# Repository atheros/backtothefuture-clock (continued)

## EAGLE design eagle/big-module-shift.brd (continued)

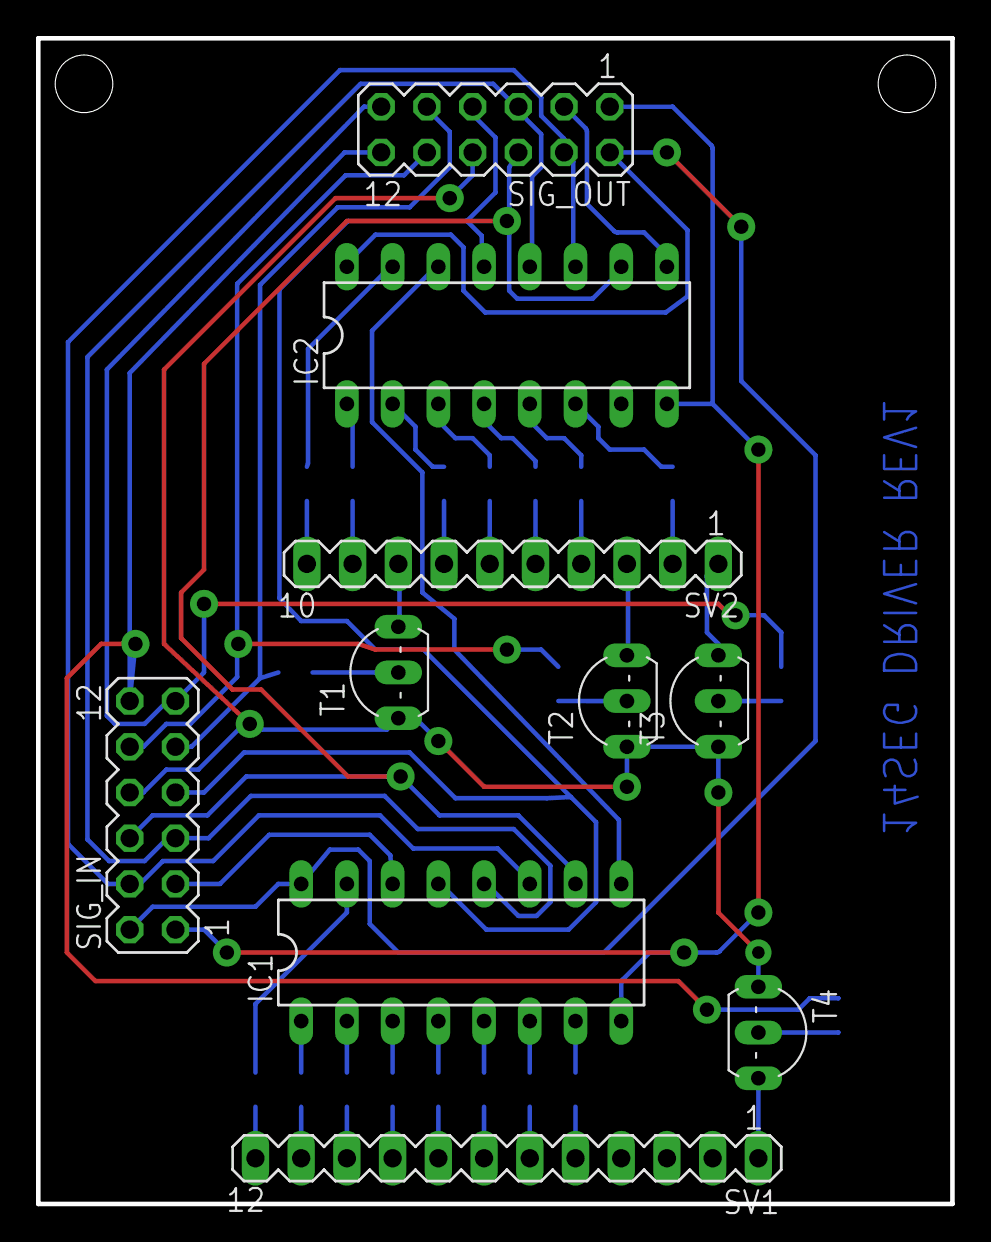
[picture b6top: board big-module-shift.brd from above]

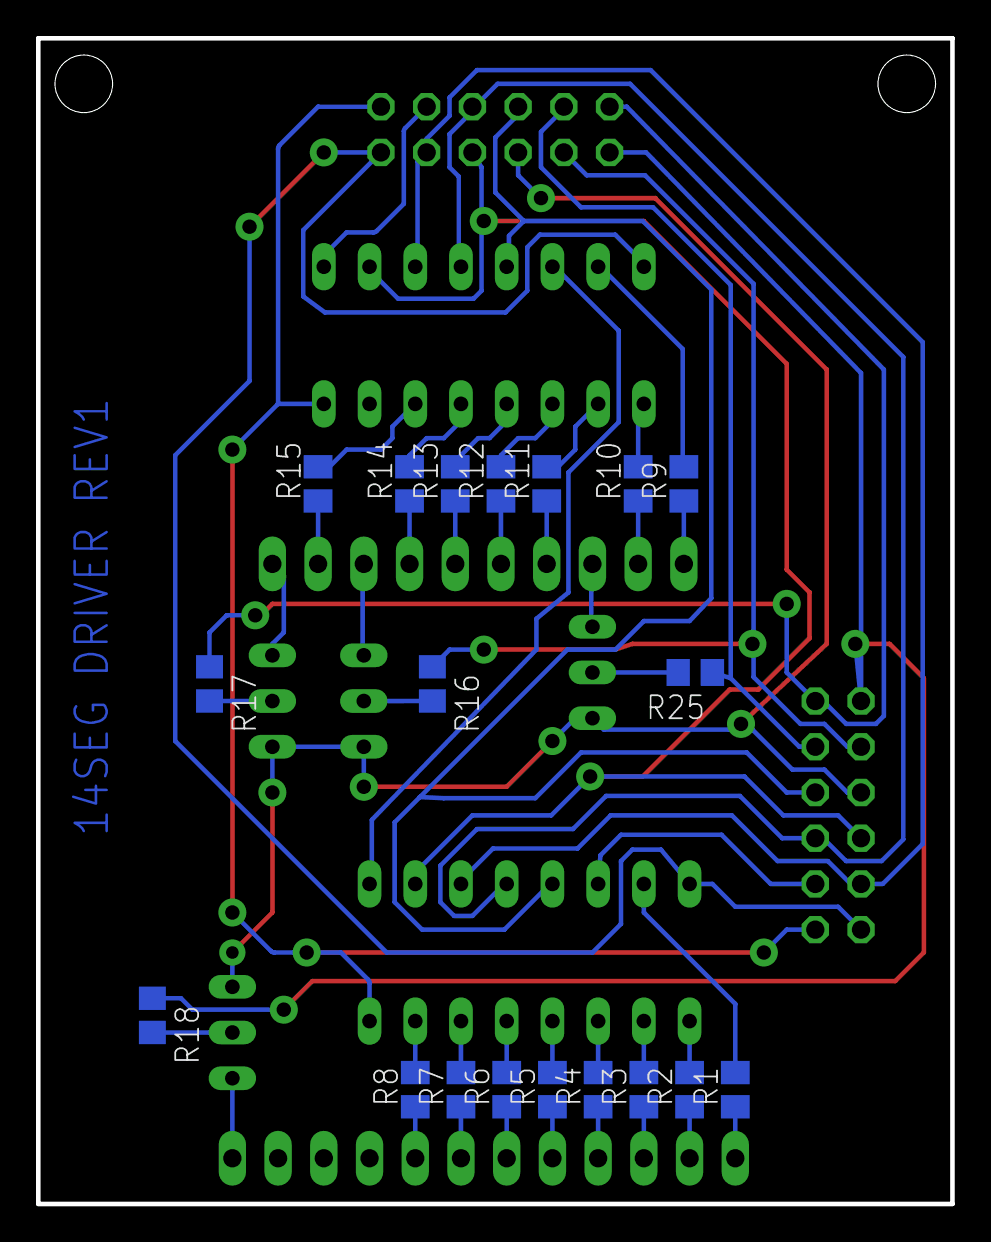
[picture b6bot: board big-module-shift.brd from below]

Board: 2 copper layers, 50.8 x 64.8 mm, 29 parts (19 on the bottom side), 52 nets.

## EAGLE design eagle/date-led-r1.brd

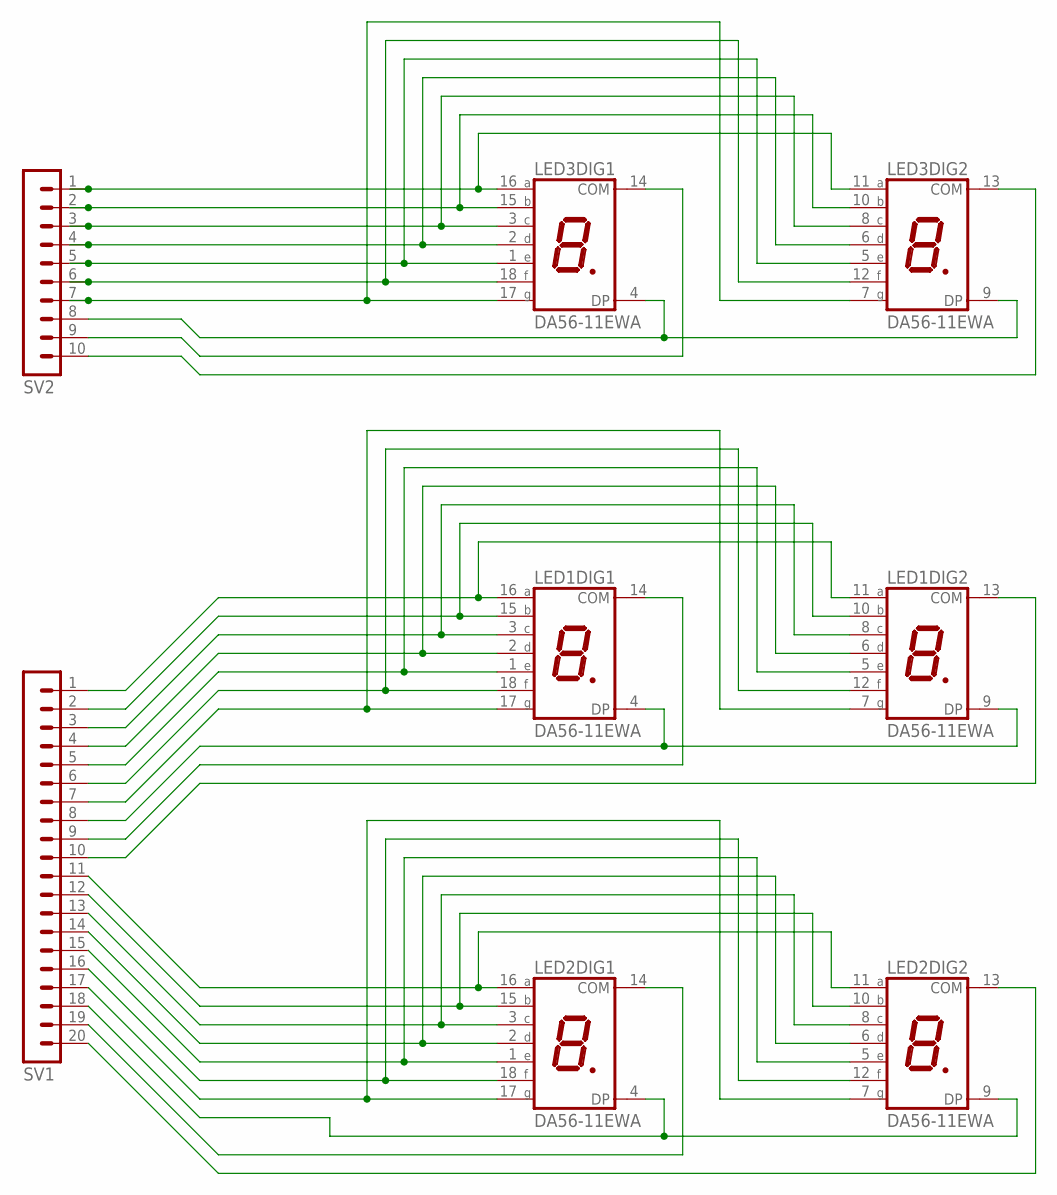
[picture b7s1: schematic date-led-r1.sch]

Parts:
LED1, LED2, LED3: DA56-11EWA; DA56
SV1: MA20-1W
SV2: MA10-1W

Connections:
unnamed: LED1.11 (A), LED1.16 (A), SV1.1
unnamed: LED1.10 (B), LED1.15 (B), SV1.2
unnamed: LED1.3 (C), LED1.8 (C), SV1.3
unnamed: LED1.2 (D), LED1.6 (D), SV1.4
unnamed: LED1.1 (E), LED1.5 (E), SV1.5
unnamed: LED1.12 (F), LED1.18 (F), SV1.6
unnamed: LED1.7 (G), LED1.17 (G), SV1.7
unnamed: LED1.4 (DP), LED1.9 (DP), SV1.8
unnamed: LED2.11 (A), LED2.16 (A), SV1.11
unnamed: LED2.10 (B), LED2.15 (B), SV1.12
unnamed: LED2.3 (C), LED2.8 (C), SV1.13
unnamed: LED2.2 (D), LED2.6 (D), SV1.14
unnamed: LED2.1 (E), LED2.5 (E), SV1.15
unnamed: LED2.12 (F), LED2.18 (F), SV1.16
unnamed: LED2.7 (G), LED2.17 (G), SV1.17
unnamed: LED2.4 (DP), LED2.9 (DP), SV1.18
unnamed: LED1.13 (COM), SV1.10
unnamed: LED3.11 (A), LED3.16 (A), SV2.1
unnamed: LED1.14 (COM), SV1.9
unnamed: LED3.10 (B), LED3.15 (B), SV2.2
unnamed: LED3.3 (C), LED3.8 (C), SV2.3
unnamed: LED3.2 (D), LED3.6 (D), SV2.4
unnamed: LED3.1 (E), LED3.5 (E), SV2.5
unnamed: LED3.12 (F), LED3.18 (F), SV2.6
unnamed: LED2.14 (COM), SV1.19
unnamed: LED2.13 (COM), SV1.20
unnamed: LED3.7 (G), LED3.17 (G), SV2.7
unnamed: LED3.4 (DP), LED3.9 (DP), SV2.8
unnamed: LED3.14 (COM), SV2.9
unnamed: LED3.13 (COM), SV2.10

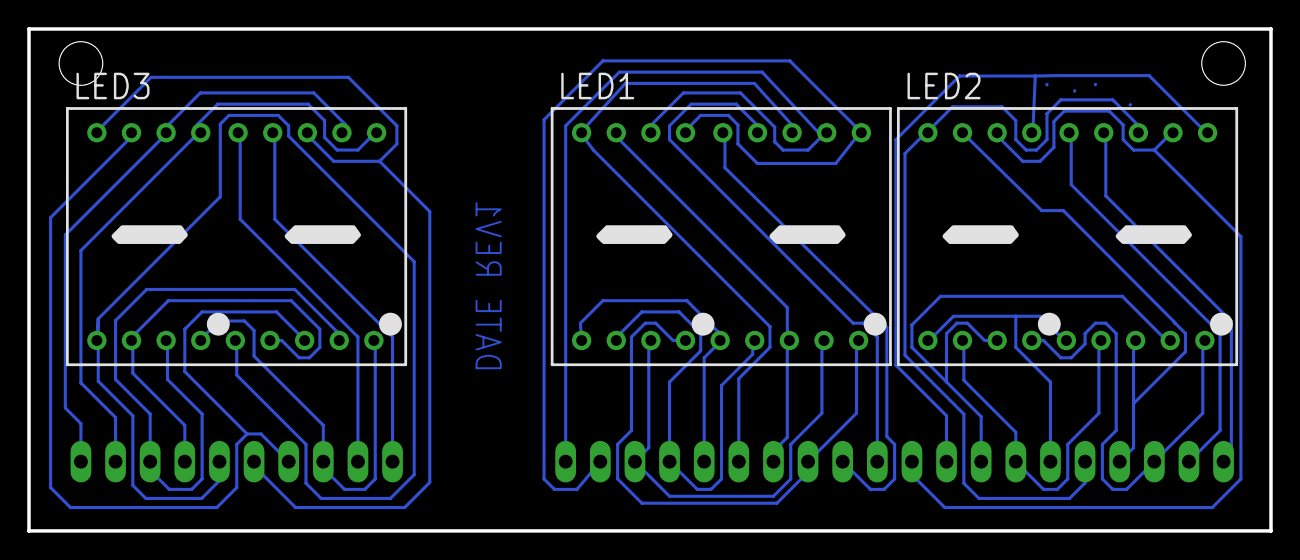
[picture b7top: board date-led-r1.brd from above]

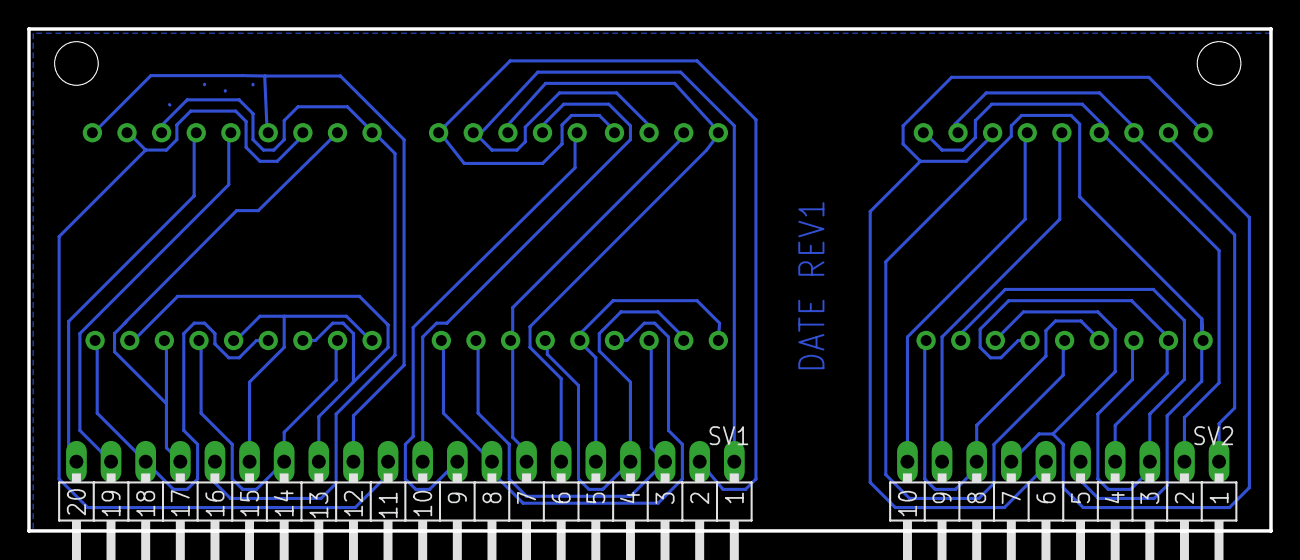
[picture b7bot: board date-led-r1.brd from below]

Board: 2 copper layers, 91.1 x 36.8 mm, 5 parts (2 on the bottom side), 30 nets.

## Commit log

2014-04-13 updates to the board
2014-04-14 Additional boards
2014-04-14 removed some backup files?
2014-04-15 Date display and driver - sorry for the driver board layout, I'll fix if I decide to use it
2014-04-17 Updated circuit and testing code
2014-04-17 Added a readme file
2014-04-19 More schematics
2014-04-19 test code driving 14 segment displays
2014-04-21 More updates
2014-04-23 Some progress
2014-04-25 Lots of schematics updates and some initial code
2014-04-26 new boards and source code
2014-04-27 Updates big and small
2014-04-28 code updates
2014-04-29 Big Update
